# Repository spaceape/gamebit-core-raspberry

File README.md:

# 1. Runtime
## 1.1. Abstract Device Tree
 - "env"
 - "mnt"
 - "dev"
 - "proc"

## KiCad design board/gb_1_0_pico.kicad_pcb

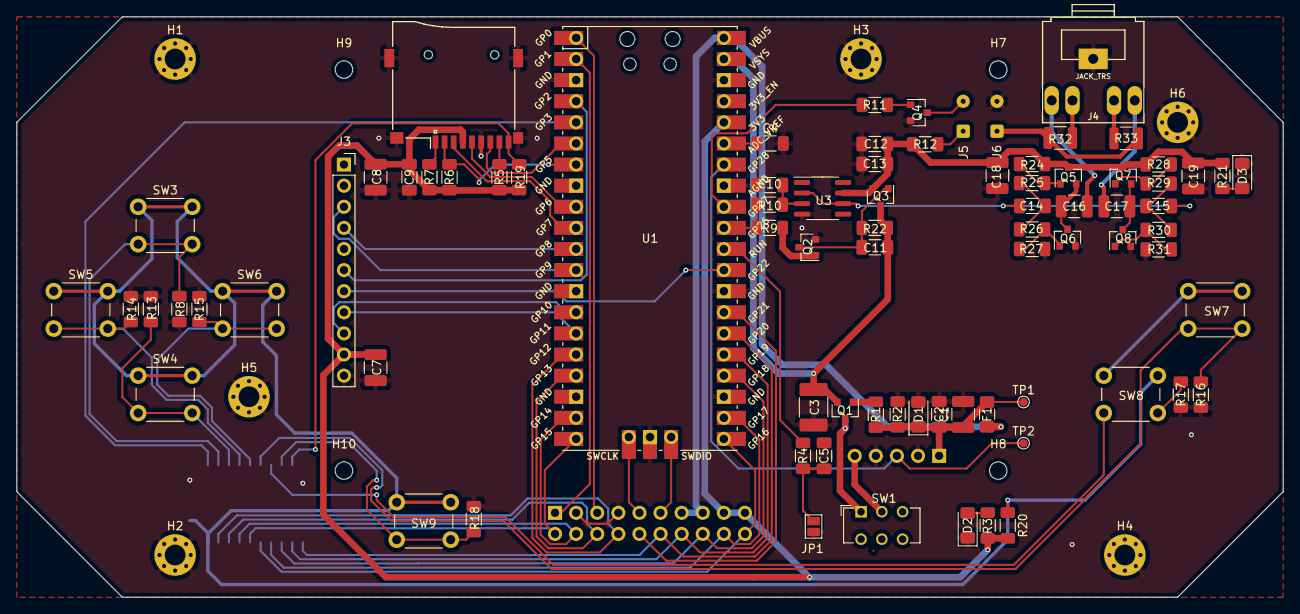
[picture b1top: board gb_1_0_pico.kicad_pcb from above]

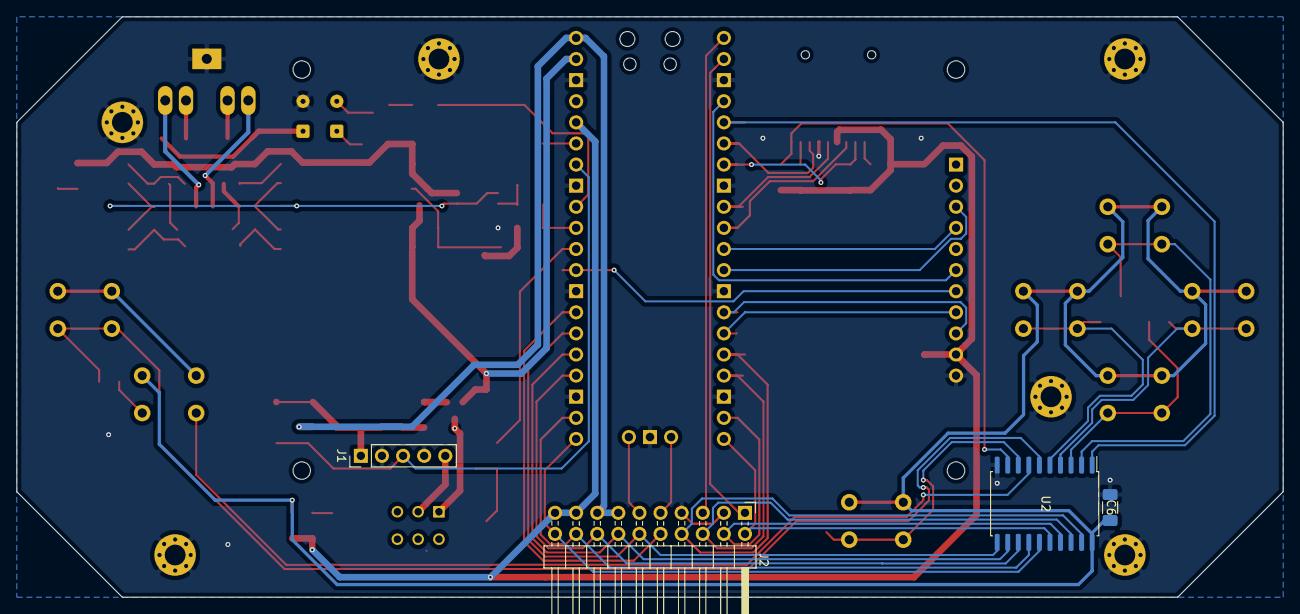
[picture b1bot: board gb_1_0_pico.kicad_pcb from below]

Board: 2 copper layers, 152.4 x 69.8 mm, 94 parts (4 on the bottom side), 73 nets.

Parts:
C1, C7, C8, C16, C17: 10µ; C_1210_3225Metric_Pad1.33x2.70mm_HandSolder
C2, C4, C5, C6, C9, C13: 100n; C_1206_3216Metric_Pad1.33x1.80mm_HandSolder
C3: 100µ; C_1812_4532Metric_Pad1.57x3.40mm_HandSolder
C10: 10n; C_1206_3216Metric_Pad1.33x1.80mm_HandSolder
C11, C12, C14, C15: 1µ; C_1206_3216Metric_Pad1.33x1.80mm_HandSolder
C18, C19: 47µ; C_1210_3225Metric_Pad1.33x2.70mm_HandSolder
D1: 5.6V; D_1206_3216Metric_Pad1.42x1.75mm_HandSolder
D2, D3: LED; LED_1206_3216Metric_Pad1.42x1.75mm_HandSolder
F1: Polyfuse; Fuse_1206_3216Metric_Pad1.42x1.75mm_HandSolder
H1, H2, H3, H4, H5, H6: MountingHole_Pad; MountingHole_2.5mm_Pad_Via
H7, H8, H9, H10: MountingHole; MountingHole_2.1mm
J1: BMC; PinHeader_1x05_P2.54mm_Vertical
J2: EXPANSION; PinHeader_2x10_P2.54mm_Horizontal
J3: 2.8'' TFT LCD; PinSocket_1x11_P2.54mm_Vertical
J4: JACK_TRS; Tayda_3.5mm_stereo_TRS_jack_A-853
J5: MOTOR; SolderWire-0.1sqmm_1x02_P3.6mm_D0.4mm_OD1mm
J6: SPEAKER; SolderWire-0.1sqmm_1x02_P3.6mm_D0.4mm_OD1mm
JP1: RESET; SolderJumper-2_P1.3mm_Open_Pad1.0x1.5mm
Q1, Q3: IRLML6402; SOT-23
Q2, Q4: IRLML2502; SOT-23
Q5, Q7: BC848; SOT-23
Q6, Q8: BC858; SOT-23
R1, R2, R9, R11: 10K; R_1206_3216Metric_Pad1.30x1.75mm_HandSolder
R3, R21: 1.2K; R_1206_3216Metric_Pad1.30x1.75mm_HandSolder
R4, R24, R27, R28, R31: 1K; R_1206_3216Metric_Pad1.30x1.75mm_HandSolder
R5, R6, R7, R22: 100K; R_1206_3216Metric_Pad1.30x1.75mm_HandSolder
R8, R13, R14, R15, R16, R17, R18, R19: 47K; R_1206_3216Metric_Pad1.30x1.75mm_HandSolder
R10: 2K; R_1206_3216Metric_Pad1.30x1.75mm_HandSolder
R12: 47; R_1206_3216Metric_Pad1.30x1.75mm_HandSolder
R20: 0R; R_1206_3216Metric_Pad1.30x1.75mm_HandSolder
R25, R26, R29, R30: 560; R_1206_3216Metric_Pad1.30x1.75mm_HandSolder
R32, R33: 0.25; R_1210_3225Metric
SW1: KlunkenSwitch; SW_CuK_JS202011CQN_DPDT_Straight
SW3: U; SW_PUSH_6mm_H4.3mm
SW4: D; SW_PUSH_6mm_H4.3mm
SW5: L; SW_PUSH_6mm_H4.3mm
SW6: R; SW_PUSH_6mm_H4.3mm
SW7: B; SW_PUSH_6mm_H4.3mm
SW8: A; SW_PUSH_6mm_H4.3mm
SW9: SELECT; SW_PUSH_6mm_H4.3mm
TP1: USB Power; TestPoint_Pad_D1.0mm
TP2: Battery Voltage; TestPoint_Pad_D1.0mm
U1: Pico; RPi_Pico_SMD_TH
U2: 74LS573; SOIC-20W_7.5x12.8mm_P1.27mm
U3: MCP601-xSN; SOIC-8_3.9x4.9mm_P1.27mm
XS1: uSD; Conn_uSDcard

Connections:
/BMCINV+: C1.1, C2.2, D1.1, F1.1, J1.1, R1.1, R2.1, TP1.1
/BMCMON: J1.3, TP2.1, U1.34
/BMCOUTV+: J1.5, SW1.2
/KB_CS: U1.5, U2.1
/KB_READ: J2.12, U1.26, U2.11
/PIN_BUS_D0: J2.8, U1.16, U2.19
/PIN_BUS_D1: J2.6, U1.17, U2.18
/PIN_BUS_D2: J2.4, U1.19, U2.17
/PIN_BUS_D3: J2.2, U1.20, U2.16
/PIN_BUS_D4: J2.20, U1.21, U2.15
/PIN_BUS_D5: J2.18, U1.22, U2.14
/PIN_BUS_D6: J2.16, U1.24, U2.13
/PIN_BUS_D7: J2.14, U1.25, U2.12
/PIN_BUS_WR: J2.10, U1.27
/PIN_LCD_CS: J3.3, U1.12
/PIN_LCD_DC: J3.6, U1.4
/PIN_LCD_RESET: J3.7, U1.29
/PIN_LCD_RX: J3.4, U1.11
/PIN_LCD_SCK: J3.9, U1.14
/PIN_LCD_TX: J3.8, U1.15
/PIN_SDC_CS: R6.2, U1.7, XS1.2
/PIN_SDC_RX: U1.6, XS1.7
/PIN_SDC_SCK: U1.9, XS1.5
/PIN_SDC_TX: U1.10, XS1.3
/SND_L: R9.1, R10.1, U1.31
/SND_LFO: R11.2, U1.32
/VAMP: C12.2, C13.2, C18.1, C19.1, Q3.2, Q5.3, Q7.3, R12.1, R21.1, R24.2, R28.2, U3.7
/VLP: C6.1, R20.1, SW3.1, SW4.1, SW5.1, SW6.1, SW7.1, SW8.1, SW9.1, U2.20
GND: C1.2, C2.1, C3.2, C4.2, C5.2, C6.2, C7.2, C8.2, C9.2, C10.2, C12.1, C13.1, C18.2, C19.2, D1.2, D2.1, D3.1, H1.1, H2.1, H3.1, H4.1, H5.1, H6.1, J1.2, J1.4, J2.3, J2.7, J3.11, J4.1, J6.2, JP1.1, Q2.2, Q4.2, Q6.2, Q8.2, R2.2, R8.2, R13.2, R14.2, R15.2, R16.2, R17.2, R18.2, R27.1, R31.1, U1.3, U1.8, U1.13, U1.18, U1.23, U1.28, U1.33, U1.38, U1.42, U2.10, U3.4, XS1.6
unnamed: C4.1, U1.35
unnamed: C5.1, JP1.2, R4.1
unnamed: C10.1, R10.2, U3.3
unnamed: C11.1, Q2.3, Q3.1, R22.1
unnamed: C14.1, C15.1, U3.2, U3.6
unnamed: C14.2, R25.1, R26.2
unnamed: C15.2, R29.1, R30.2
unnamed: C16.1, Q5.2, Q6.3
unnamed: C16.2, J4.3
unnamed: C17.1, Q7.2, Q8.3
unnamed: C17.2, J4.2
unnamed: D2.2, R3.2
unnamed: D3.2, R21.2
unnamed: J2.1, U1.2
unnamed: J2.5, U1.1
unnamed: J2.9, U1.41
unnamed: J2.11, U1.43
unnamed: J4.4, R33.1
unnamed: J4.5, R32.1
unnamed: J5.1, R12.2
unnamed: J5.2, Q4.3
unnamed: J6.1, R32.2, R33.2
unnamed: Q1.1, R1.2
unnamed: Q1.3, SW1.1
unnamed: Q2.1, R9.2
unnamed: Q4.1, R11.1
unnamed: Q5.1, R24.1, R25.2
unnamed: Q6.1, R26.1, R27.2
unnamed: Q7.1, R28.1, R29.2
unnamed: Q8.1, R30.1, R31.2
unnamed: R4.2, U1.30
unnamed: R5.2, XS1.8
unnamed: R7.2, XS1.1
unnamed: R8.1, SW3.2, U2.2
unnamed: R13.1, SW4.2, U2.3
unnamed: R14.1, SW5.2, U2.4
unnamed: R15.1, SW6.2, U2.5
unnamed: R16.1, SW7.2, U2.6
unnamed: R17.1, SW8.2, U2.7
unnamed: R18.1, SW9.2, U2.8
unnamed: R19.2, U2.9, XS1.9
VBUS: F1.2, J2.13, J2.15, U1.40
VCOR: C7.1, C8.1, C9.1, J2.17, J2.19, J3.10, R3.1, R5.1, R6.1, R7.1, R19.1, R20.2, U1.36, XS1.4
VSYS: C3.1, C11.2, Q1.2, Q3.3, R22.2, U1.39

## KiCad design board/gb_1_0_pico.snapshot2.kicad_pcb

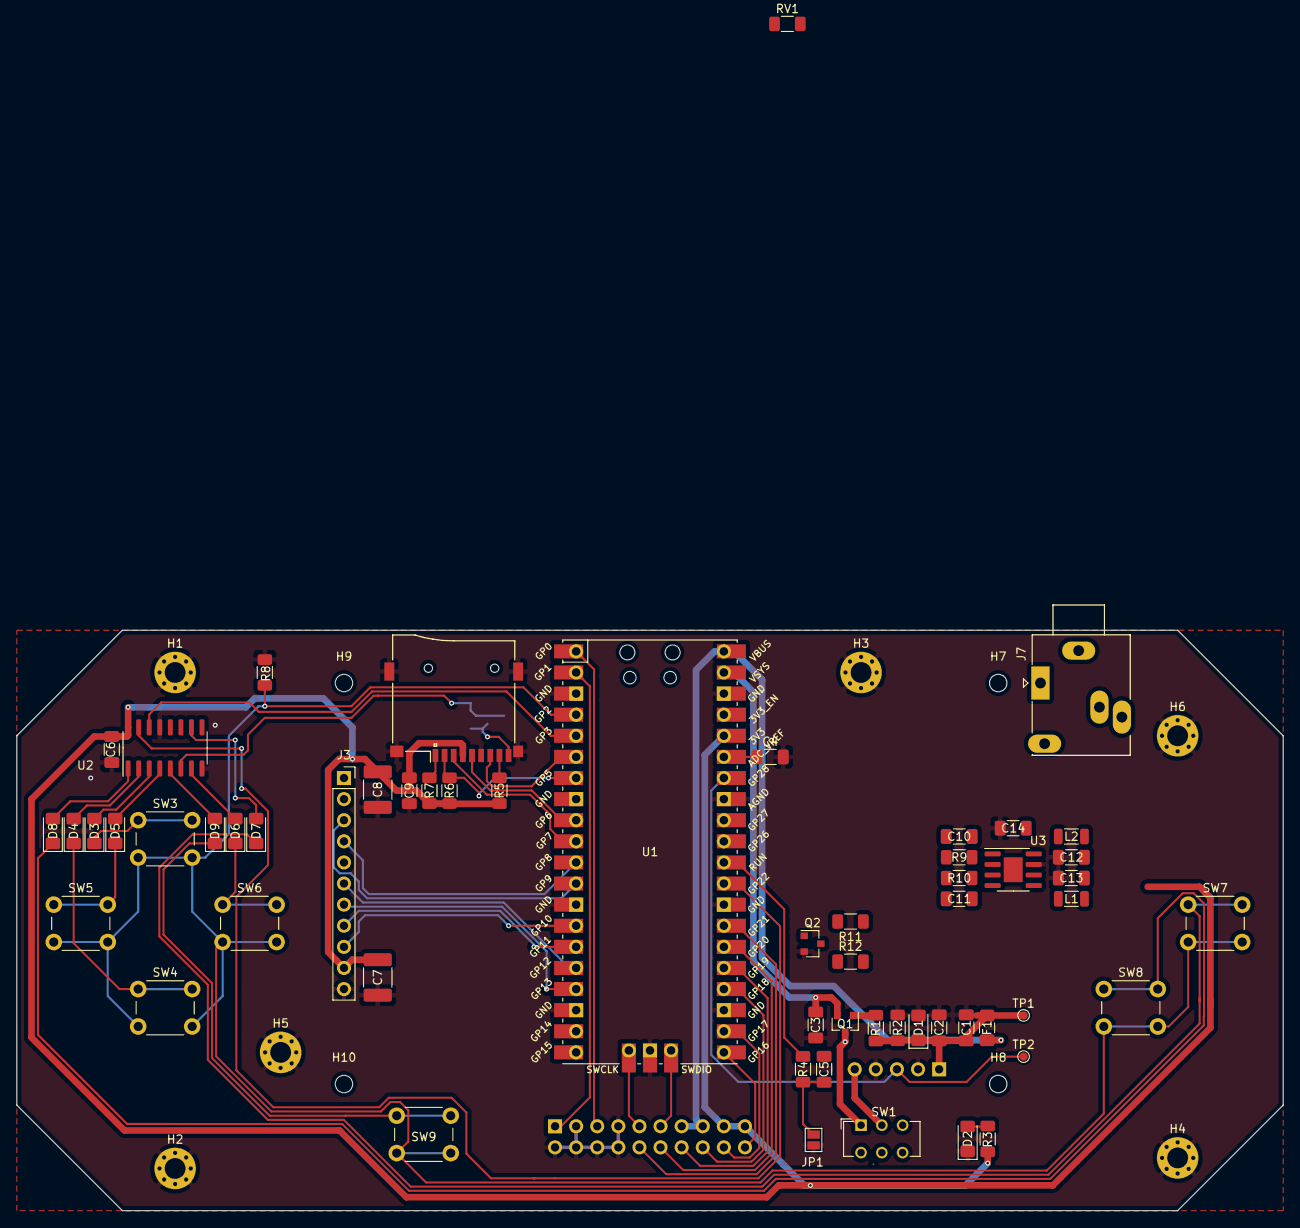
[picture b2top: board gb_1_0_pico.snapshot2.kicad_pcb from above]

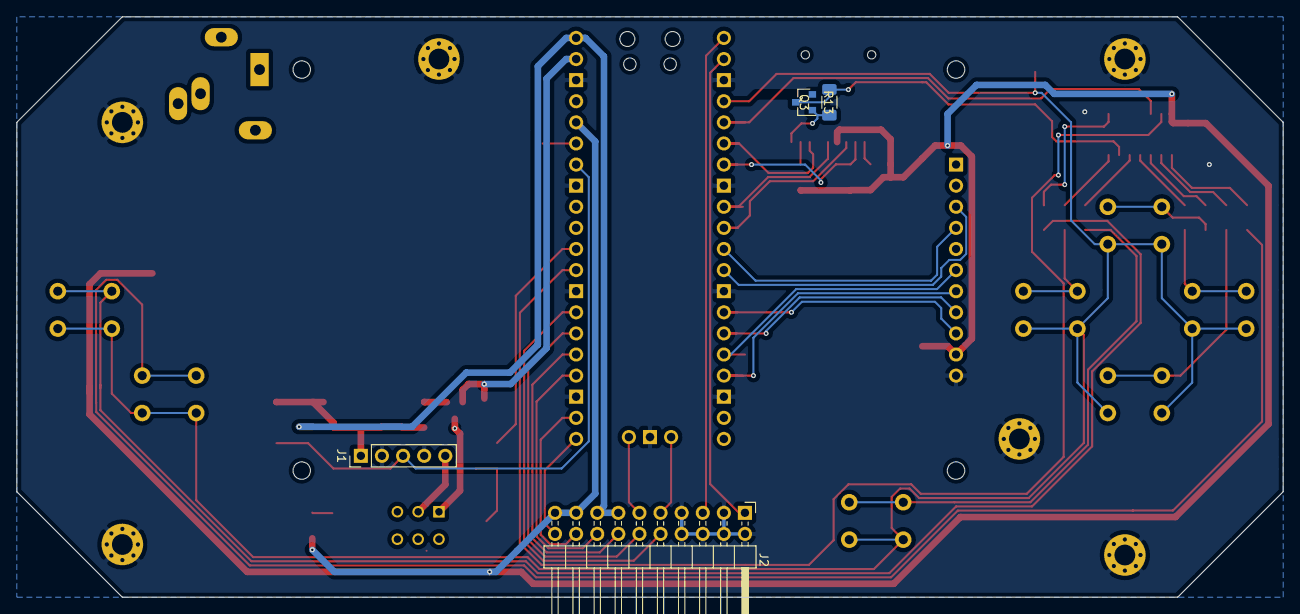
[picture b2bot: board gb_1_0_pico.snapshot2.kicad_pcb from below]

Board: 2 copper layers, 152.4 x 69.9 mm, 72 parts (4 on the bottom side), 68 nets.

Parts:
C1: 10µ; C_1206_3216Metric_Pad1.33x1.80mm_HandSolder
C2, C4, C5, C6, C9: 100n; C_1206_3216Metric_Pad1.33x1.80mm_HandSolder
C3: 100µ; C_1206_3216Metric_Pad1.33x1.80mm_HandSolder
C7: 10µ; C_1812_4532Metric_Pad1.57x3.40mm_HandSolder
C8: 100µ; C_1812_4532Metric_Pad1.57x3.40mm_HandSolder
C10, C11, C14: 1µ; C_1206_3216Metric_Pad1.33x1.80mm_HandSolder
C12, C13: 100p; C_1206_3216Metric_Pad1.33x1.80mm_HandSolder
D1: 5.6V; D_1206_3216Metric_Pad1.42x1.75mm_HandSolder
D2: LED; LED_1206_3216Metric_Pad1.42x1.75mm_HandSolder
D3, D4, D5, D6, D7, D8, D9: D; D_1206_3216Metric_Pad1.42x1.75mm_HandSolder
F1: Polyfuse; Fuse_1206_3216Metric_Pad1.42x1.75mm_HandSolder
H1, H2, H3, H4, H5, H6: MountingHole_Pad; MountingHole_2.5mm_Pad_Via
H7, H8, H9, H10: MountingHole; MountingHole_2.1mm
J1: BMC; PinHeader_1x05_P2.54mm_Vertical
J2: EXPANSION; PinHeader_2x10_P2.54mm_Horizontal
J3: 2.8'' TFT LCD; PinSocket_1x11_P2.54mm_Vertical
J7: AudioJack3_SwitchTR; Jack_3.5mm_Ledino_KB3SPRS_Horizontal
JP1: RESET; SolderJumper-2_P1.3mm_Open_Pad1.0x1.5mm
L1, L2: L; L_1206_3216Metric
Q1, Q3: IRLML6402; SOT-23
Q2: BC848; SOT-23
R1, R2: R; R_1206_3216Metric_Pad1.30x1.75mm_HandSolder
R3: 1.2K; R_1206_3216Metric_Pad1.30x1.75mm_HandSolder
R4, R11: 1K; R_1206_3216Metric_Pad1.30x1.75mm_HandSolder
R5, R6, R7: 100K; R_1206_3216Metric_Pad1.30x1.75mm_HandSolder
R8: 47K; R_1206_3216Metric_Pad1.30x1.75mm_HandSolder
R9, R10: 100; R_1206_3216Metric_Pad1.30x1.75mm_HandSolder
R12: 47; R_1206_3216Metric_Pad1.30x1.75mm_HandSolder
R13: 4.7k; R_1206_3216Metric_Pad1.30x1.75mm_HandSolder
RV1: 10K; R_1206_3216Metric_Pad1.30x1.75mm_HandSolder
SW1: KlunkenSwitch; SW_CuK_JS202011CQN_DPDT_Straight
SW3: U; SW_PUSH_6mm_H4.3mm
SW4: D; SW_PUSH_6mm_H4.3mm
SW5: L; SW_PUSH_6mm_H4.3mm
SW6: R; SW_PUSH_6mm_H4.3mm
SW7: B; SW_PUSH_6mm_H4.3mm
SW8: A; SW_PUSH_6mm_H4.3mm
SW9: SELECT; SW_PUSH_6mm_H4.3mm
TP1: USB Power; TestPoint_Pad_D1.0mm
TP2: Battery Voltage; TestPoint_Pad_D1.0mm
U1: Pico; RPi_Pico_SMD_TH
U2: 4017; SOIC-16_3.9x9.9mm_P1.27mm
U3: PAM8302AAD; SOIC-8-1EP_3.9x4.9mm_P1.27mm_EP2.29x3mm
XS1: uSD; Conn_uSDcard

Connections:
/BMCINV+: C1.1, C2.2, D1.1, F1.1, J1.1, R1.1, R2.1, TP1.1
/BMCMON: J1.3, TP2.1, U1.34
/BMCOUTV+: J1.5, SW1.2
/KBI: Q3.2, R8.1, SW3.2, SW4.2, SW5.2, SW6.2, SW7.2, SW8.2, SW9.2, U1.4
/KB_RESET: U1.29, U2.15
/KB_SCK: U1.5, U2.14
/PIN_BUS_RD: J2.12, U1.26
/PIN_BUS_WR: J2.10, U1.27
/PIN_LCD_CS: J3.3, U1.12
/PIN_LCD_DC: J3.6, U1.16
/PIN_LCD_RESET: J3.7, U1.17
/PIN_LCD_RX: J3.4, U1.11
/PIN_LCD_SCK: J3.9, U1.14
/PIN_LCD_TX: J3.8, U1.15
/PIN_LFO: R11.2, U1.32
/PIN_SDC_CS: R6.2, U1.7, XS1.2
/PIN_SDC_RX: U1.6, XS1.7
/PIN_SDC_SCK: U1.9, XS1.5
/PIN_SDC_TX: U1.10, XS1.3
/PIN_SND_L: RV1.1, U1.31
/PWEN: U1.37, U3.1
GND: C1.2, C2.1, C3.2, C4.2, C5.2, C6.2, C7.2, C8.2, C9.2, C12.2, C13.2, C14.1, D1.2, D2.1, H1.1, H2.1, H3.1, H4.1, H5.1, H6.1, J1.2, J1.4, J2.2, J2.3, J2.4, J2.6, J2.7, J2.8, J3.11, JP1.1, Q2.2, R2.2, R8.2, U1.3, U1.8, U1.13, U1.18, U1.23, U1.28, U1.33, U1.38, U1.42, U2.8, U2.13, U3.7, XS1.6
unnamed: C4.1, U1.35
unnamed: C5.1, JP1.2, R4.1
unnamed: C10.1, RV1.2
unnamed: C10.2, R9.2
unnamed: C11.1, R10.2
unnamed: C12.1, L2.1, U3.8
unnamed: C13.1, L1.1, U3.5
unnamed: D2.2, R3.2
unnamed: D3.1, SW3.1
unnamed: D3.2, U2.3
unnamed: D4.1, SW4.1
unnamed: D4.2, U2.2
unnamed: D5.1, SW5.1
unnamed: D5.2, U2.4
unnamed: D6.1, SW6.1
unnamed: D6.2, U2.7
unnamed: D7.1, SW7.1
unnamed: D7.2, U2.10
unnamed: D8.1, SW8.1
unnamed: D8.2, U2.1
unnamed: D9.1, SW9.1
unnamed: D9.2, U2.5
unnamed: J2.1, U1.2
unnamed: J2.5, U1.1
unnamed: J2.9, U1.41
unnamed: J2.11, U1.43
unnamed: J2.14, U1.25
unnamed: J2.16, U1.24
unnamed: J2.18, U1.22
unnamed: J2.20, U1.21
unnamed: J7.RN, J7.TN
unnamed: J7.S, L2.2
unnamed: J7.R, J7.T, L1.2
unnamed: Q1.1, R1.2
unnamed: Q1.3, SW1.1
unnamed: Q2.1, R11.1
unnamed: Q3.1, R13.2, XS1.9
unnamed: Q3.3, R13.1, U2.6
unnamed: R4.2, U1.30
unnamed: R5.2, XS1.8
unnamed: R7.2, XS1.1
unnamed: R9.1, U3.3
unnamed: R10.1, U3.4
VBUS: F1.2, J2.13, J2.15, U1.40
VCOR: C6.1, C7.1, C8.1, C9.1, C14.2, J2.17, J2.19, J3.10, R3.1, R5.1, R6.1, R7.1, R12.1, U1.36, U2.16, U3.6, XS1.4
VSYS: C3.1, Q1.2, U1.39

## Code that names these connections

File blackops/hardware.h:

#ifndef bops_hardware_h
#define bops_hardware_h
/** 
    Copyright (c) 2022, wicked systems
    All rights reserved.

    Redistribution and use in source and binary forms, with or without modification, are permitted provided that the following
    conditions are met:
    * Redistributions of source code must retain the above copyright notice, this list of conditions and the following
      disclaimer.
    * Redistributions in binary form must reproduce the above copyright notice, this list of conditions and the following 
      disclaimer in the documentation and/or other materials provided with the distribution.
    * Neither the name of wicked systems nor the names of its contributors may be used to endorse or promote products derived
      from this software without specific prior written permission.

    THIS SOFTWARE IS PROVIDED BY THE COPYRIGHT HOLDERS AND CONTRIBUTORS "AS IS" AND ANY EXPRESS OR IMPLIED WARRANTIES,
    INCLUDING, BUT NOT LIMITED TO, THE IMPLIED WARRANTIES OF MERCHANTABILITY AND FITNESS FOR A PARTICULAR PURPOSE ARE
    DISCLAIMED. IN NO EVENT SHALL THE COPYRIGHT HOLDER OR CONTRIBUTORS BE LIABLE FOR ANY DIRECT, INDIRECT, INCIDENTAL, 
    SPECIAL, EXEMPLARY, OR CONSEQUENTIAL DAMAGES (INCLUDING, BUT NOT LIMITED TO, PROCUREMENT OF SUBSTITUTE GOODS OR SERVICES;
    LOSS OF USE, DATA, OR PROFITS; OR BUSINESS INTERRUPTION) HOWEVER CAUSED AND ON ANY THEORY OF LIABILITY, WHETHER IN 
    CONTRACT, STRICT LIABILITY, OR TORT (INCLUDING NEGLIGENCE OR OTHERWISE) ARISING IN ANY WAY OUT OF THE USE OF THIS SOFTWARE,
    EVEN IF ADVISED OF THE POSSIBILITY OF SUCH DAMAGE.
**/
#include <sys.h>

/* hw_power_hard
*/
constexpr bool hw_power_hard = true;

/* hw_enable_uart0
*/
constexpr bool hw_enable_uart0 = true;

/* pin_uart0_*
   pin assignments for uart0
*/
constexpr unsigned int  pin_uart0_rx = 1;
constexpr unsigned int  pin_uart0_tx = 0;

/* hw_enable_uart1
*/
constexpr bool hw_enable_uart1 = false;

/* pin_uart1_*
   pin assignments for uart1
*/
constexpr unsigned int  pin_uart1_rx = pin_none;
constexpr unsigned int  pin_uart1_tx = pin_none;

/* hw_default_uart_baud
*/
constexpr long int  hw_default_uart_baud = 115200;

/* hw_enable_spi0
*/
constexpr bool  hw_enable_spi0 = true;

/* pin_spi0_*
   pin assignments for spi0
*/
constexpr unsigned int  pin_spi0_rx = 4;
constexpr unsigned int  pin_spi0_tx = 7;
constexpr unsigned int  pin_spi0_sck = 6;

/* hw_enable_spi1
*/
constexpr bool hw_enable_spi1 = true;

/* pin_spi1_*
   pin assignments for spi1
*/
constexpr unsigned int  pin_spi1_rx = 8;
constexpr unsigned int  pin_spi1_tx = 11;
constexpr unsigned int  pin_spi1_sck = 10;

/* hw_default_spi
   whether or not to add an ADT entry for a default 'spi' device and which spi instance that should point to
*/
constexpr auto hw_default_spi_index = -1;

/* hw_default_spi_baud
*/
constexpr long int  hw_default_spi_baud = 16777216;

/* hw_enable_sdc
   initialise SD card on the selected SPI interface
   requires: SPI
*/
constexpr bool hw_enable_sdc = false;
constexpr char hw_sdc_bus[]  = "/dev/spi";

/* pin_sdc_*
   default SD Card pins (SPI1)
*/
constexpr unsigned int  pin_sdc_cs = 9;
constexpr unsigned int  pin_sdc_led = PICO_DEFAULT_LED_PIN;   // SD Card activity LED (0 - disable)

/* hw_enable_lcd
   initialise LCD on the selected SPI interface
   requires: SPI
*/
constexpr bool hw_enable_lcd = true;
constexpr char hw_lcd_bus[]  = "/dev/spi0";

/* pin_lcd_*
   default LCD pins (SPI0)
*/
constexpr unsigned int  pin_lcd_cs = 5;
constexpr unsigned int  pin_lcd_ds = 9;
constexpr unsigned int  pin_lcd_reset = 8;

/* hw_enable_controller (always)
   boot up the EMC controller
   requires: UART
*/
// constexpr bool hw_enable_controller = true;
constexpr char hw_controller_io[]  = "/dev/uart0";

/* pin_dbg
   debug pin
*/
constexpr unsigned int  pin_dbg = 22;

#endif

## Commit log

2021-03-29 initial, LCD demos
2021-04-06 dev@210406 - basic sd && fat support
2021-04-07 dev@210407 - file stream for the far-from-complete SD and FS support libraries
2021-04-07 dev@210407 - fat demo code + minor FS fix
2021-04-11 dev@2104011 - established source dir + skeleton ELF loader
2021-04-14 dev@210414 - loader code updates
2021-04-21 dev@210421
2021-04-23 dev@210423
2022-03-24 dev@220324
2022-11-23 dev@221123
2022-11-25 dev@221125
2022-12-11 dev@221211
2022-12-11 Removing ULD as a built-in library
2022-12-11 Removing GFX as a built-in library
2022-12-11 Established `gfx` and `uld` as submodules
